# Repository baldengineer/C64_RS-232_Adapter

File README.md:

# C64_RS-232_Adapter
 RS232 Adapter for the Commodore User Port

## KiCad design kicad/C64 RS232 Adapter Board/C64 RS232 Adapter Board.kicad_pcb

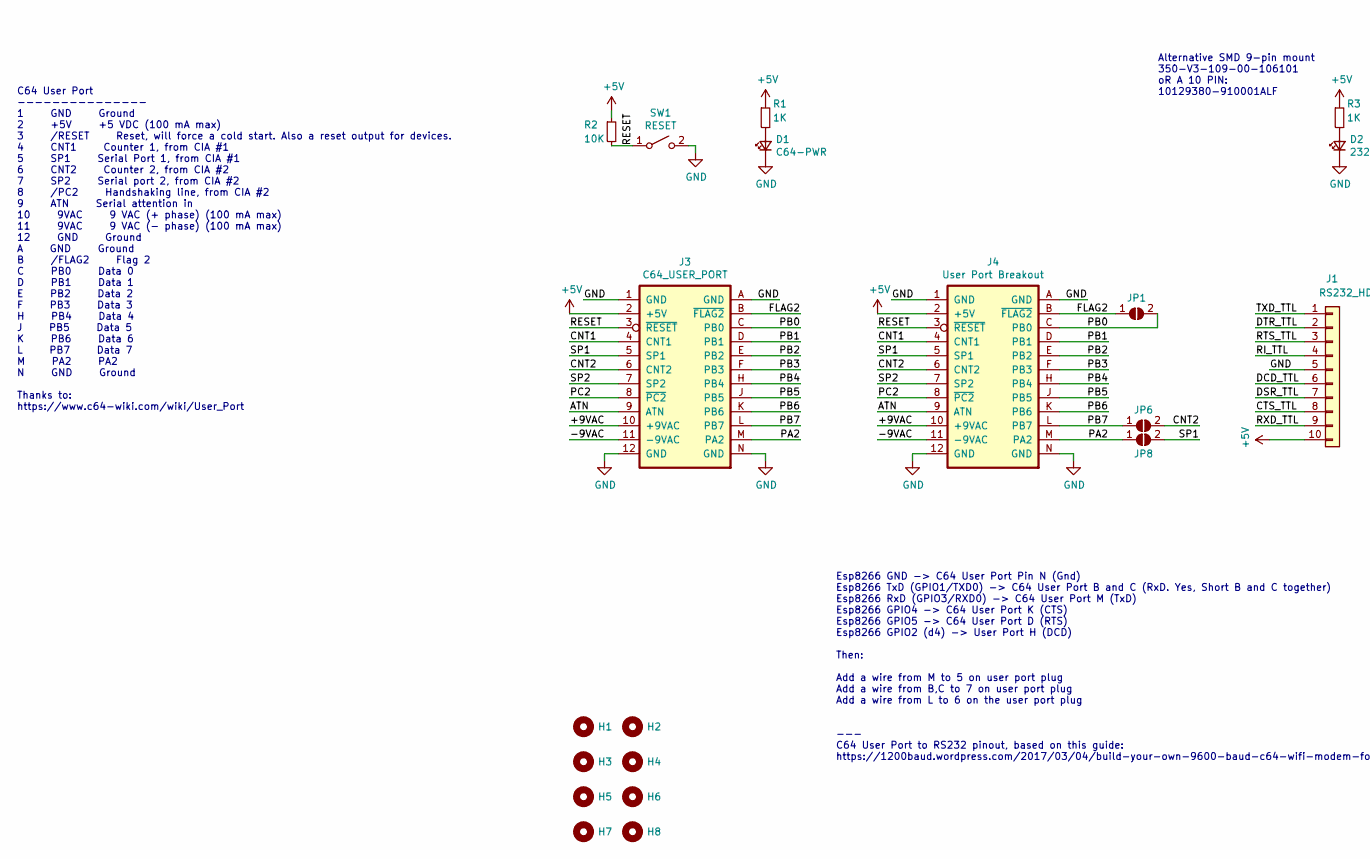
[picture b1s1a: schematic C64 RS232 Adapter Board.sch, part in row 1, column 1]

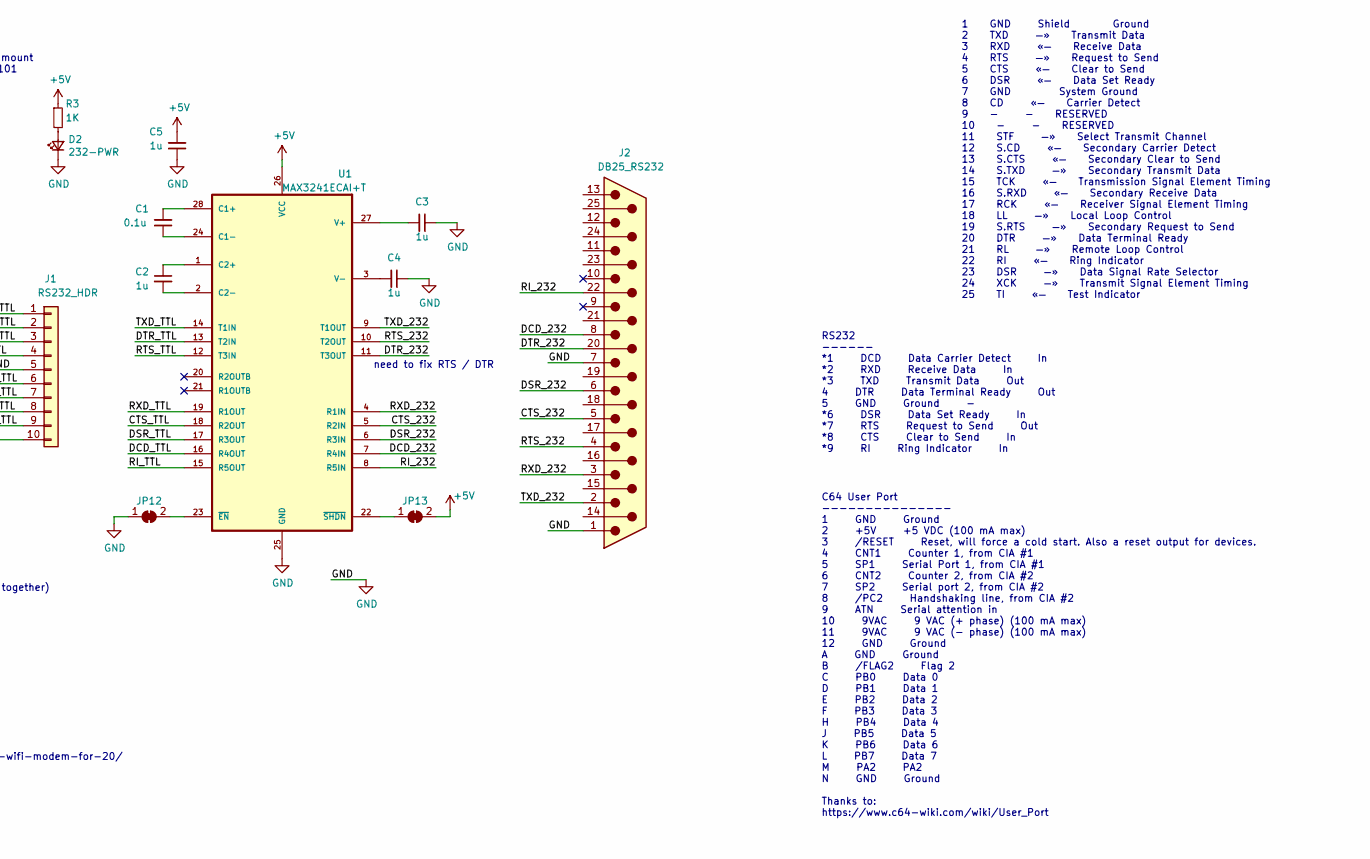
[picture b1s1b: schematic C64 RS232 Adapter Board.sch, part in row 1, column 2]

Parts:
C1: 0.1u; C_0805_2012Metric_Pad1.15x1.40mm_HandSolder
C2, C3, C4, C5: 1u; C_0805_2012Metric_Pad1.15x1.40mm_HandSolder
D1: C64-PWR; LED_1206_3216Metric_Pad1.42x1.75mm_HandSolder
D2: 232-PWR; LED_1206_3216Metric_Pad1.42x1.75mm_HandSolder
H1, H2, H3, H4, H5, H6, H7, H8: MountingHole; MountingHole_2.5mm
J1: RS232_HDR; PinHeader_1x10_P2.54mm_Vertical
J2: DB25_RS232; DSUB-25_Male_EdgeMount_P2.77mm
J3: C64_USER_PORT; 0.156-2x12
J4: User Port Breakout; C64_2.54mm_User_Port
JP1, JP6, JP8: SolderJumper_2_Bridged; SolderJumper-2_P1.3mm_Open_TrianglePad1.0x1.5mm
JP12, JP13: SolderJumper_2_Bridged; SolderJumper-2_P1.3mm_Bridged_RoundedPad1.0x1.5mm
R1, R3: 1K; R_0805_2012Metric_Pad1.15x1.40mm_HandSolder
R2: 10K; R_0805_2012Metric_Pad1.15x1.40mm_HandSolder
SW1: RESET; Pushbutton-SMD-TL3305-2-Pad
U1: MAX3241ECAI+T; SSOP-28_5.3x10.2mm_P0.65mm

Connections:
+5V: C5.2, J1.10, J3.2 (+5V), J4.2 (+5V), JP13.2 (B), R1.1, R2.1, R3.1, U1.26 (VCC)
/+9VAC: J3.10 (+9VAC), J4.10 (+9VAC)
/-9VAC: J3.11 (-9VAC), J4.11 (-9VAC)
/ATN: J3.9 (ATN), J4.9 (ATN)
/CNT1: J3.4 (CNT1), J4.4 (CNT1)
/CNT2: J3.6 (CNT2), J4.6 (CNT2), JP6.2 (B)
/CTS_232: J2.5, U1.5 (R2IN)
/CTS_TTL: J1.8, U1.18 (R2OUT)
/DCD_232: J2.8, U1.7 (R4IN)
/DCD_TTL: J1.6, U1.16 (R4OUT)
/DSR_232: J2.6, U1.6 (R3IN)
/DSR_TTL: J1.7, U1.17 (R3OUT)
/DTR_232: J2.20, U1.11 (T3OUT)
/DTR_TTL: J1.2, U1.13 (T2IN)
/FLAG2: J3.B (~FLAG2), J4.B (~FLAG2), JP1.1 (A)
/PA2: J3.M (PA2), J4.M (PA2), JP8.1 (A)
/PB0: J3.C (PB0), J4.C (PB0), JP1.2 (B)
/PB1: J3.D (PB1), J4.D (PB1)
/PB2: J3.E (PB2), J4.E (PB2)
/PB3: J3.F (PB3), J4.F (PB3)
/PB4: J3.H (PB4), J4.H (PB4)
/PB5: J3.J (PB5), J4.J (PB5)
/PB6: J3.K (PB6), J4.K (PB6)
/PB7: J3.L (PB7), J4.L (PB7), JP6.1 (A)
/PC2: J3.8 (~PC2), J4.8 (~PC2)
/RESET: J3.3 (~RESET), J4.3 (~RESET), R2.2, SW1.1 (A)
/RI_232: J2.22, U1.8 (R5IN)
/RI_TTL: J1.4, U1.15 (R5OUT)
/RTS_232: J2.4, U1.10 (T2OUT)
/RTS_TTL: J1.3, U1.12 (T3IN)
/RXD_232: J2.3, U1.4 (R1IN)
/RXD_TTL: J1.9, U1.19 (R1OUT)
/SP1: J3.5 (SP1), J4.5 (SP1), JP8.2 (B)
/SP2: J3.7 (SP2), J4.7 (SP2)
/TXD_232: J2.2, U1.9 (T1OUT)
/TXD_TTL: J1.1, U1.14 (T1IN)
GND: C3.1, C4.1, C5.1, D1.1 (K), D2.1 (K), J1.5, J2.1, J2.7, J3.1 (GND), J3.12 (GND), J3.A (GND), J3.N (GND), J4.1 (GND), J4.12 (GND), J4.A (GND), J4.N (GND), JP12.1 (A), SW1.2 (B), U1.25 (GND)
unnamed: C1.1, U1.24 (C1-)
unnamed: C1.2, U1.28 (C1+)
unnamed: C2.1, U1.1 (C2+)
unnamed: C2.2, U1.2 (C2-)
unnamed: C3.2, U1.27 (V+)
unnamed: C4.2, U1.3 (V-)
unnamed: D1.2 (A), R1.2
unnamed: D2.2 (A), R3.2
unnamed: JP12.2 (B), U1.23 (~EN~)
unnamed: JP13.1 (A), U1.22 (~SHDN~)

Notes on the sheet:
C64 User Port --------------- 1 GND Ground 2 +5V +5 VDC (100 mA max) 3 /RESET Reset, will force a cold start. Also a reset output for devices. 4 CNT1 Counter 1, from CIA #1 5 SP1 Serial Port 1, from CIA #1 6 CNT2 Counter 2, from CIA #2 7 SP2 Serial port 2, from CIA #2 8 /PC2 Handshaking line, from 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
RS232 ------ *1 DCD Data Carrier Detect In *2 RXD Receive Data In *3 TXD Transmit Data Out 4 DTR Data Terminal Ready Out 5 GND Ground - *6 DSR Data Set Ready In *7 RTS Request to Send Out *8 CTS Clear to Send In *9 RI Ring Indicator In
1 GND Shield Ground 2 TXD —» Transmit Data 3 RXD «— Receive Data 4 RTS —» Request to Send 5 CTS «— Clear to Send 6 DSR «— Data Set Ready 7 GND System Ground 8 CD «— Carrier Detect 9 - - RESERVED 10 - - RESERVED 11 STF —» Select Transmit Channel 12 S.CD «— Secondary Carrier Detect 13 S.CTS «— Second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
Esp8266 GND -> C64 User Port Pin N (Gnd) Esp8266 TxD (GPIO1/TXD0) -> C64 User Port B and C (RxD. Yes, Short B and C together) Esp8266 RxD (GPIO3/RXD0) -> C64 User Port M (TxD) Esp8266 GPIO4 -> C64 User Port K (CTS) Esp8266 GPIO5 -> C64 User Port D (RTS) Esp8266 GPIO2 (d4) -> User Port H (DCD) Then: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
Alternative SMD 9-pin mount 350-V3-109-00-106101 oR A 10 PIN: 10129380-910001ALF
need to fix RTS / DTR

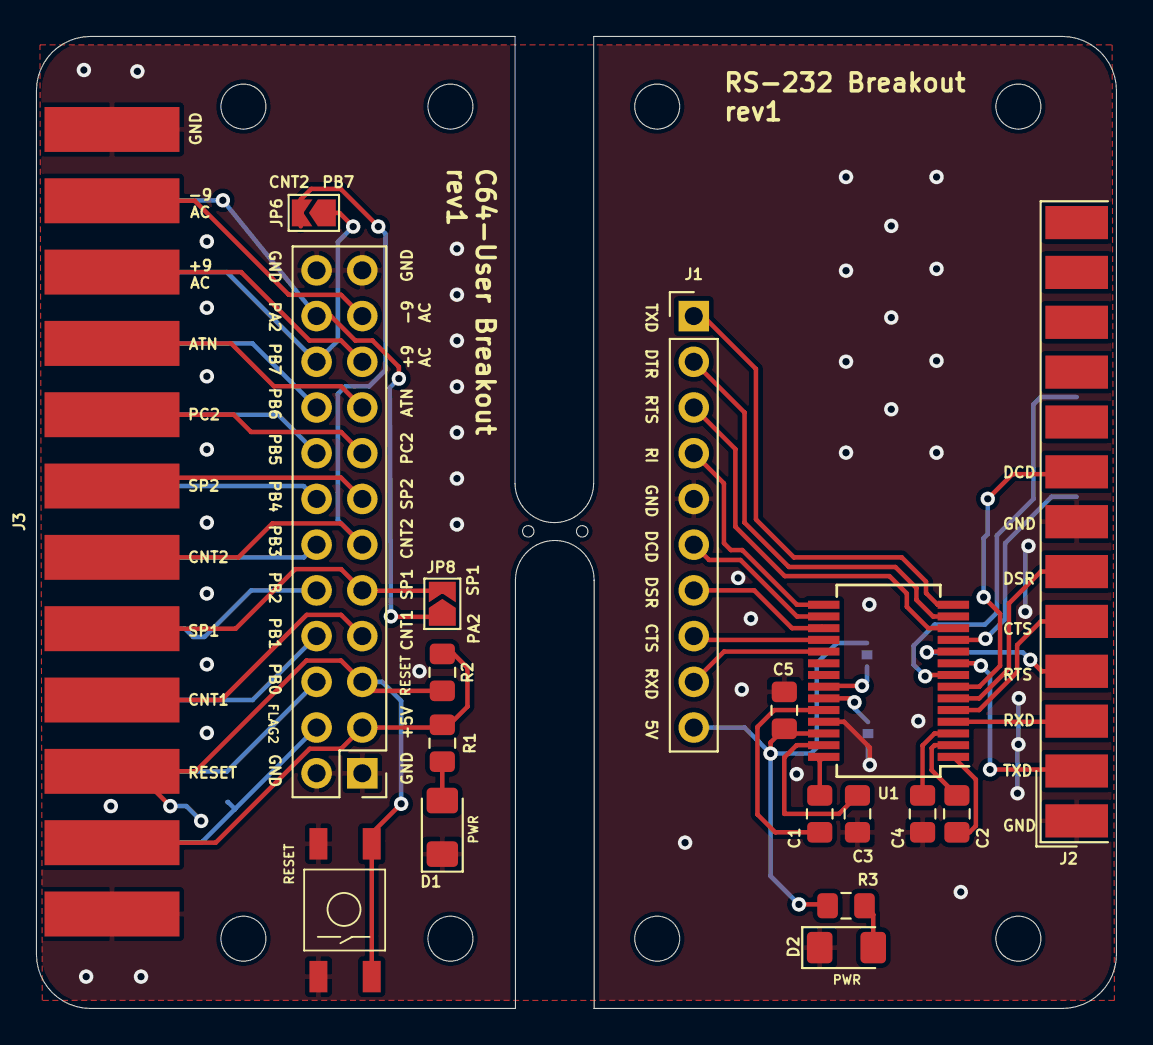
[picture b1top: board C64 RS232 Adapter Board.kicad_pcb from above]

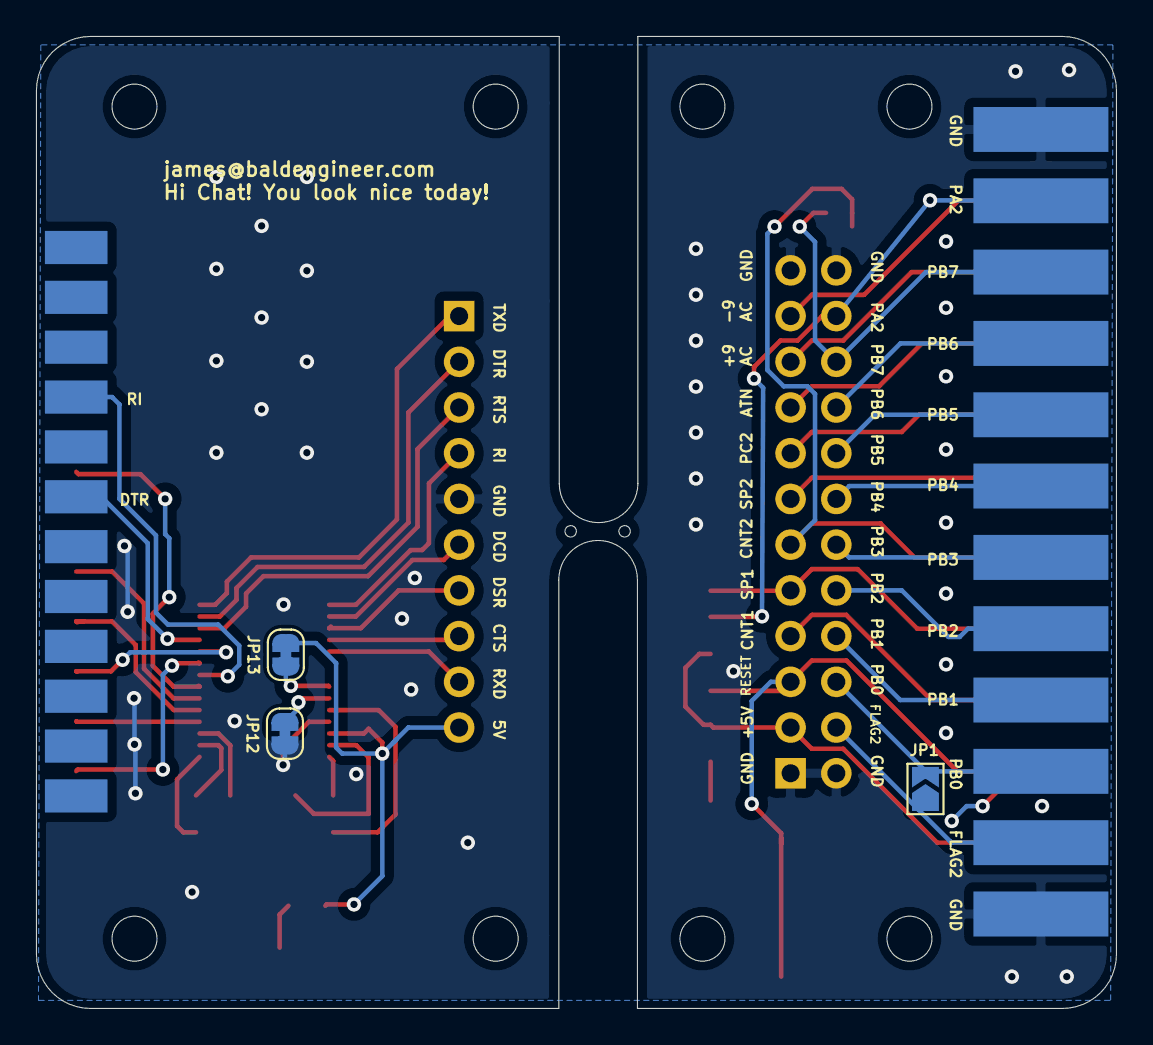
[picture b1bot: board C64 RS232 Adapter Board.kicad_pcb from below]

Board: 2 copper layers, 60.0 x 54.0 mm, 30 parts (3 on the bottom side), 47 nets.

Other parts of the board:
e: 25mil_Hole

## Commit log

2020-07-23 Cleaned up MAX3241
2020-07-23 Replaced with ESD version of 3241
2020-07-23 Finished schematic
2020-07-30 Finalized footprints, annotated, ready for PCB
2020-07-30 First pass of part layout
2020-07-30 before first routing attempt
2020-07-30 Tried this layout but don't like it
    Instead of going a 2nd time, going to try creating two boards instead
2020-07-30 going back to old
2020-07-30 commit for some reason
2020-07-30 Revert "Finalized footprints, annotated, ready for PCB"
    This reverts commit 011ea2abb4183e5d68d7ef9bd51261a9d7b16297.
2020-07-30 I dont get this at all
2020-07-30 Whew Dropbox fixed it.
2020-07-31 added vias
2020-07-31 moved pinouts around
2020-07-31 232 signals routed clean
2020-07-31 First layout done
2020-08-06 rounded the corner yo
2020-08-06 add some labels or something and stuff
2020-08-06 let's do that!
2020-08-06 Final Board (maybe?)
2020-08-22 Add Mask Layer Back of Port Conn
2021-03-22 removed 3d files
